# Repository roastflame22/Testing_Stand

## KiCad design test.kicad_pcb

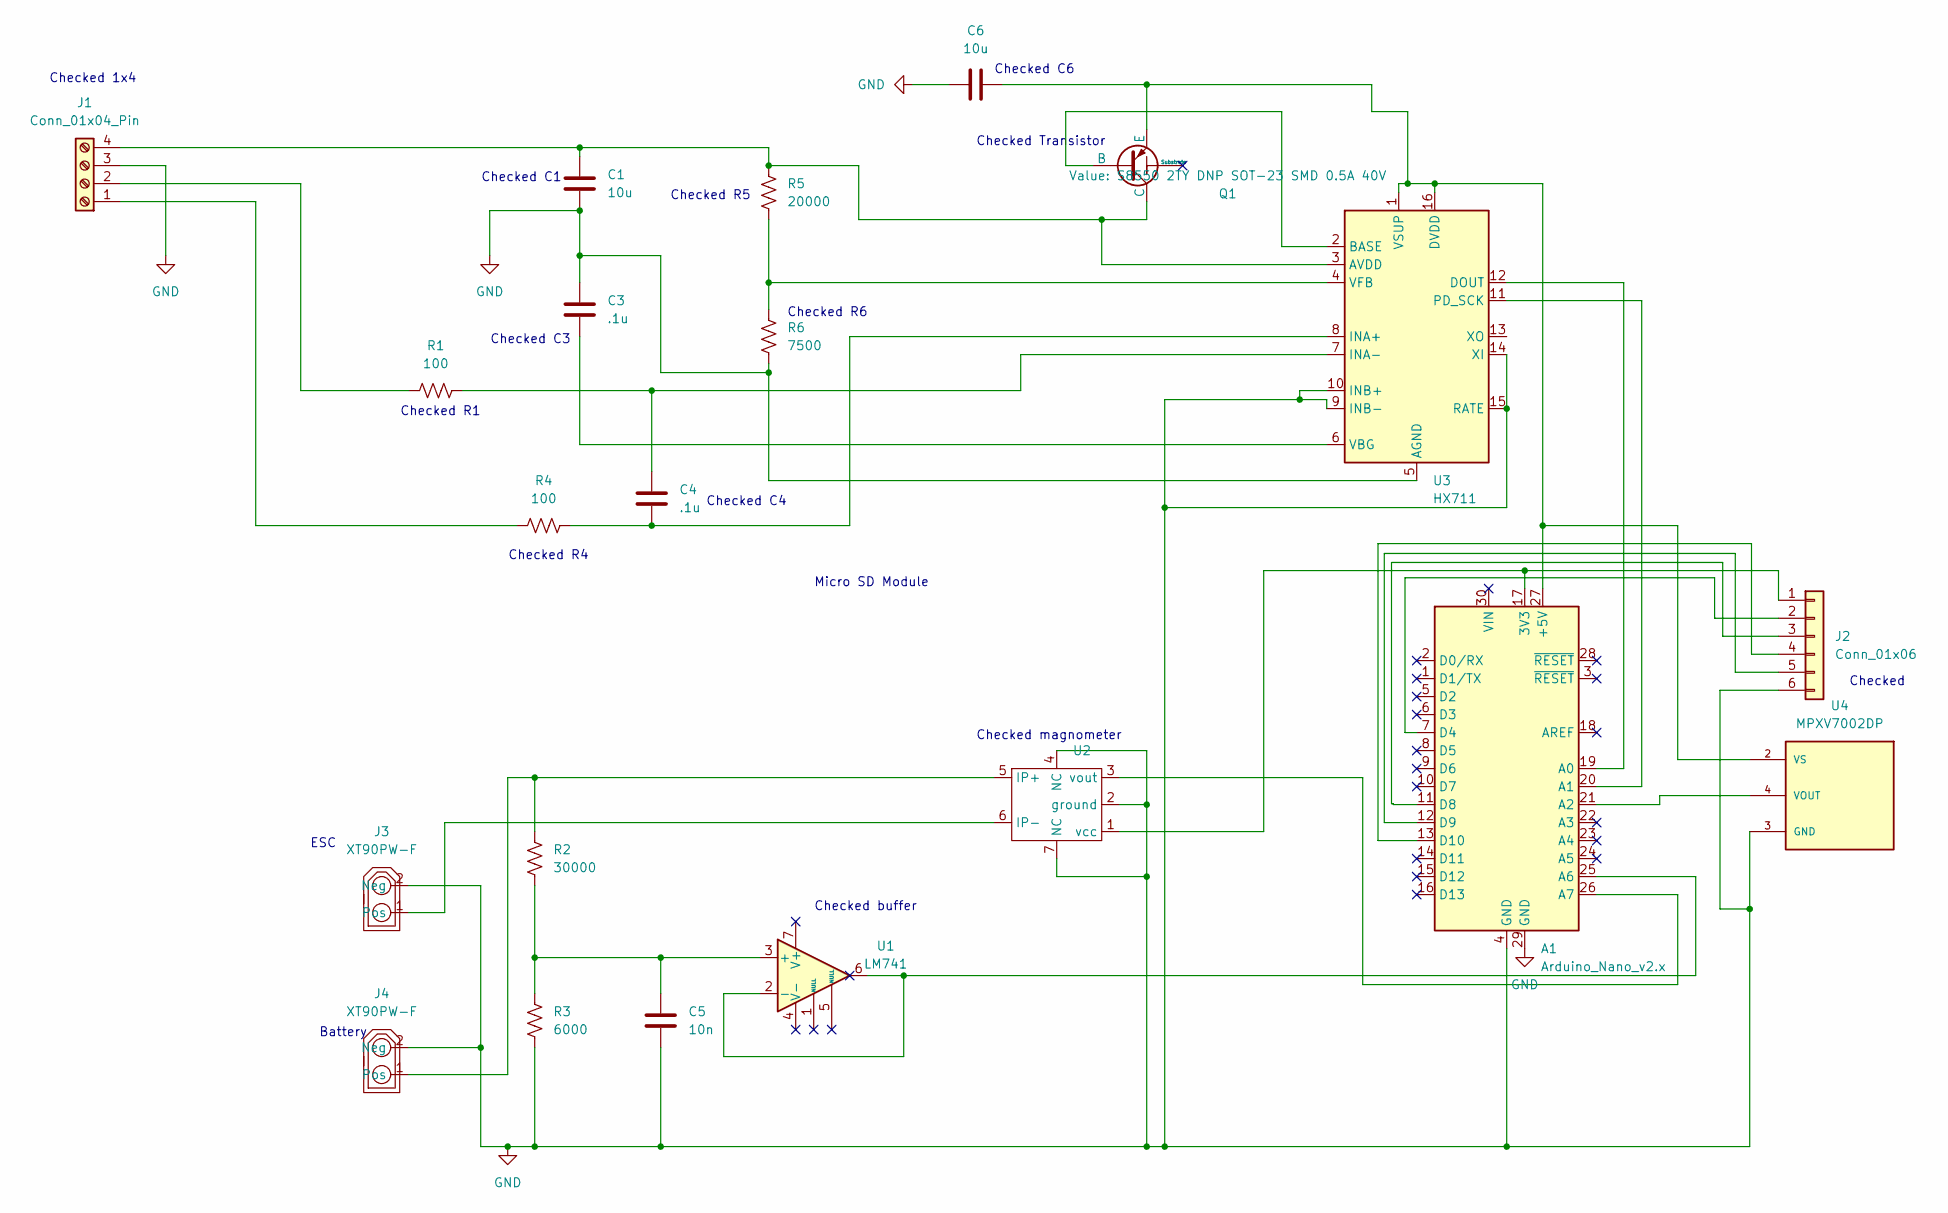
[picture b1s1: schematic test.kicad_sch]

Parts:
A1: Arduino_Nano_v2.x; Arduino_Nano
C1, C6: 10u; Capacitor_4mm_diam_.6mm_pin
C3, C4: .1u; Capacitor_4mm_diam_.6mm_pin
C5: 10n; Capacitor_4mm_diam_.6mm_pin
J1: Conn_01x04_Pin; JST_EH_B4B-EH-A_1x04_P2.50mm_Vertical
J2: Conn_01x06; JST_EH_B6B-EH-A_1x06_P2.50mm_Vertical
J3, J4: XT90PW-F; XT90_-F; PARTREV V00
Q1: S8550 2TY DNP SOT-23 SMD 0.5A 40V; SOT-23
R1, R4: 100; R_1watt
R2: 30000; R_1watt
R3: 6000; R_1watt
R5: 20000; R_1watt
R6: 7500; R_1watt
U1: LM741; SOIC-8_W3.9mm
U2: ACS781LLRTR-100U-T
U3: HX711; SOP-16_3.9x9.9mm_P1.27mm
U4: MPXV7002DP; XDCR_MPXV7002DP; PARTREV 4

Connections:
GND: A1.4 (GND), A1.29 (GND), C1.2, C3.1, C5.2, C6.2, J1.3, J2.6, J3.2 (Neg), J4.2 (Neg), R3.2, R6.2, U2.2 (ground), U2.4 (NC), U2.7 (NC), U3.5 (AGND), U3.9 (INB-), U3.10 (INB+), U3.14 (XI), U3.15 (RATE), U4.3 (GND)
unnamed: A1.17 (3V3), J2.1, U2.1 (vcc)
unnamed: A1.27 (+5V), C6.1, Q1.3 (E), U3.1 (VSUP), U3.16 (DVDD), U4.2 (VS)
unnamed: A1.19 (A0), U3.12 (DOUT)
unnamed: A1.20 (A1), U3.11 (PD_SCK)
unnamed: A1.21 (A2), U4.4 (VOUT)
unnamed: A1.25 (A6), U1.2 (-), U1.6
unnamed: A1.26 (A7), U2.3 (vout)
unnamed: A1.7 (D4), J2.2
unnamed: A1.11 (D8), J2.3
unnamed: A1.12 (D9), J2.5
unnamed: A1.13 (D10), J2.4
unnamed: J1.1, R4.1
unnamed: J1.2, R1.1
unnamed: C1.1, J1.4, Q1.1 (C), R5.1, U3.3 (AVDD)
unnamed: J3.1 (Pos), U2.6 (IP-)
unnamed: J4.1 (Pos), R2.1, U2.5 (IP+)
unnamed: Q1.2 (B), U3.2 (BASE)
unnamed: C5.1, R2.2, R3.1, U1.3 (+)
unnamed: C4.2, R4.2, U3.8 (INA+)
unnamed: C4.1, R1.2, U3.7 (INA-)
unnamed: C3.2, U3.6 (VBG)
unnamed: R5.2, R6.1, U3.4 (VFB)

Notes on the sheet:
Checked R4
Checked R6
Checked Transistor
Checked R1
Checked C3
Checked C1
Battery
ESC
Checked R5
Micro SD Module
Checked
Checked 1x4
Checked magnometer
Checked C4
Checked buffer
Checked C6

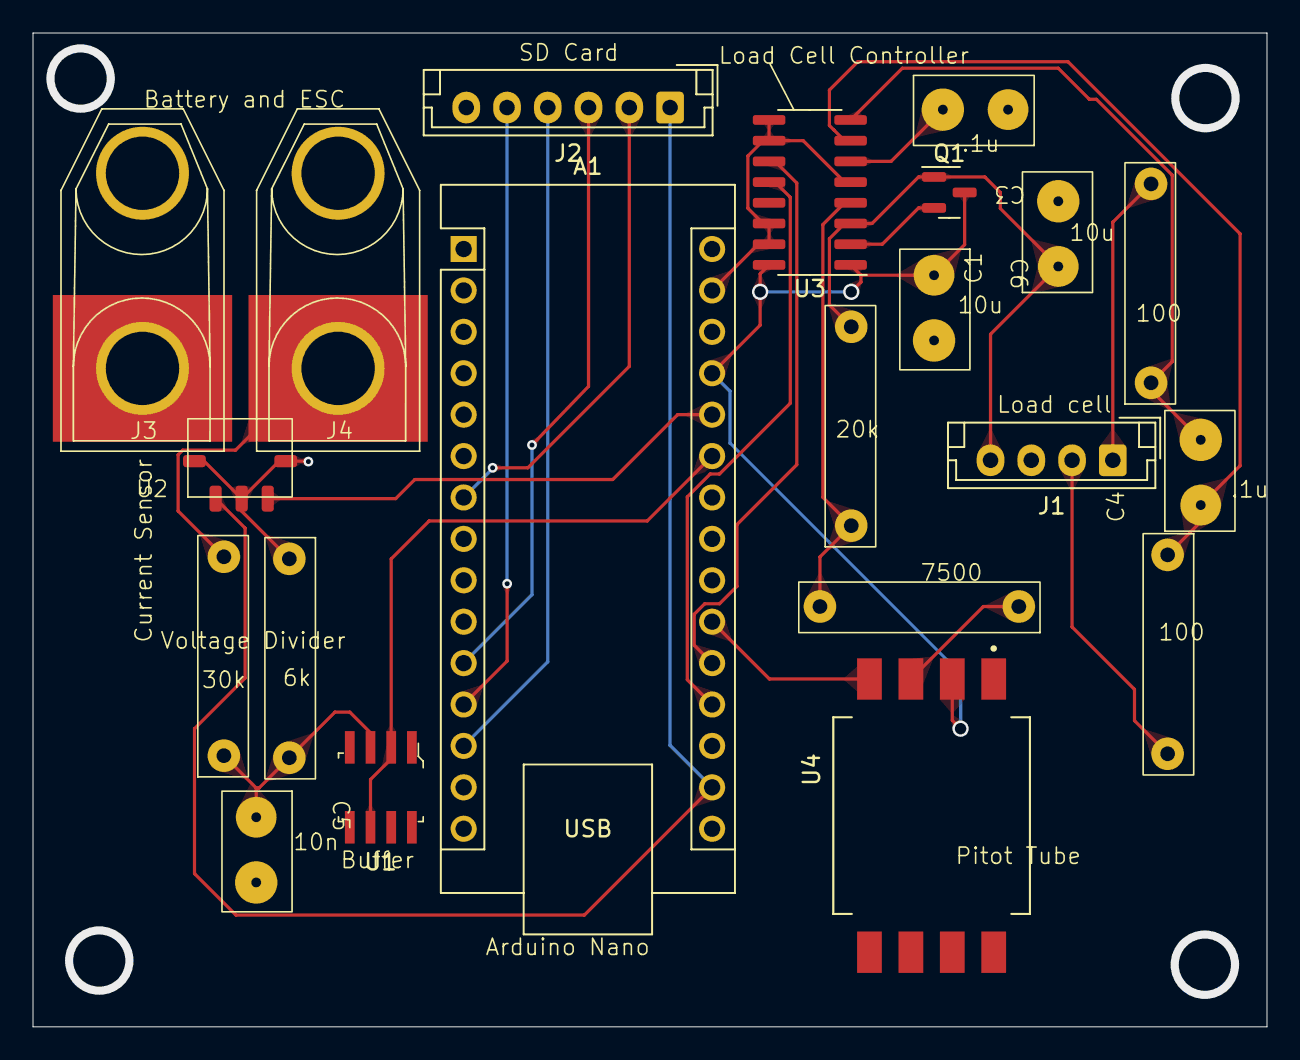
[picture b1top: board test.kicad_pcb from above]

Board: 2 copper layers, 75.7 x 61.0 mm, 21 parts (0 on the bottom side), 23 nets.

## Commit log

2023-11-03 gitignore
2023-11-03 remove lock files
2023-11-03 also delete autosave cause we forgot to
2023-11-03 Replaced test files
2023-11-15 Raymond fixed nets and added SD card module
2023-12-01 Fixed the sd card reader pins
2023-12-01 Fixed the SD card
2023-12-07 added labels to PCB
2023-12-14 Fixed caps and generated the gerber and drill files
